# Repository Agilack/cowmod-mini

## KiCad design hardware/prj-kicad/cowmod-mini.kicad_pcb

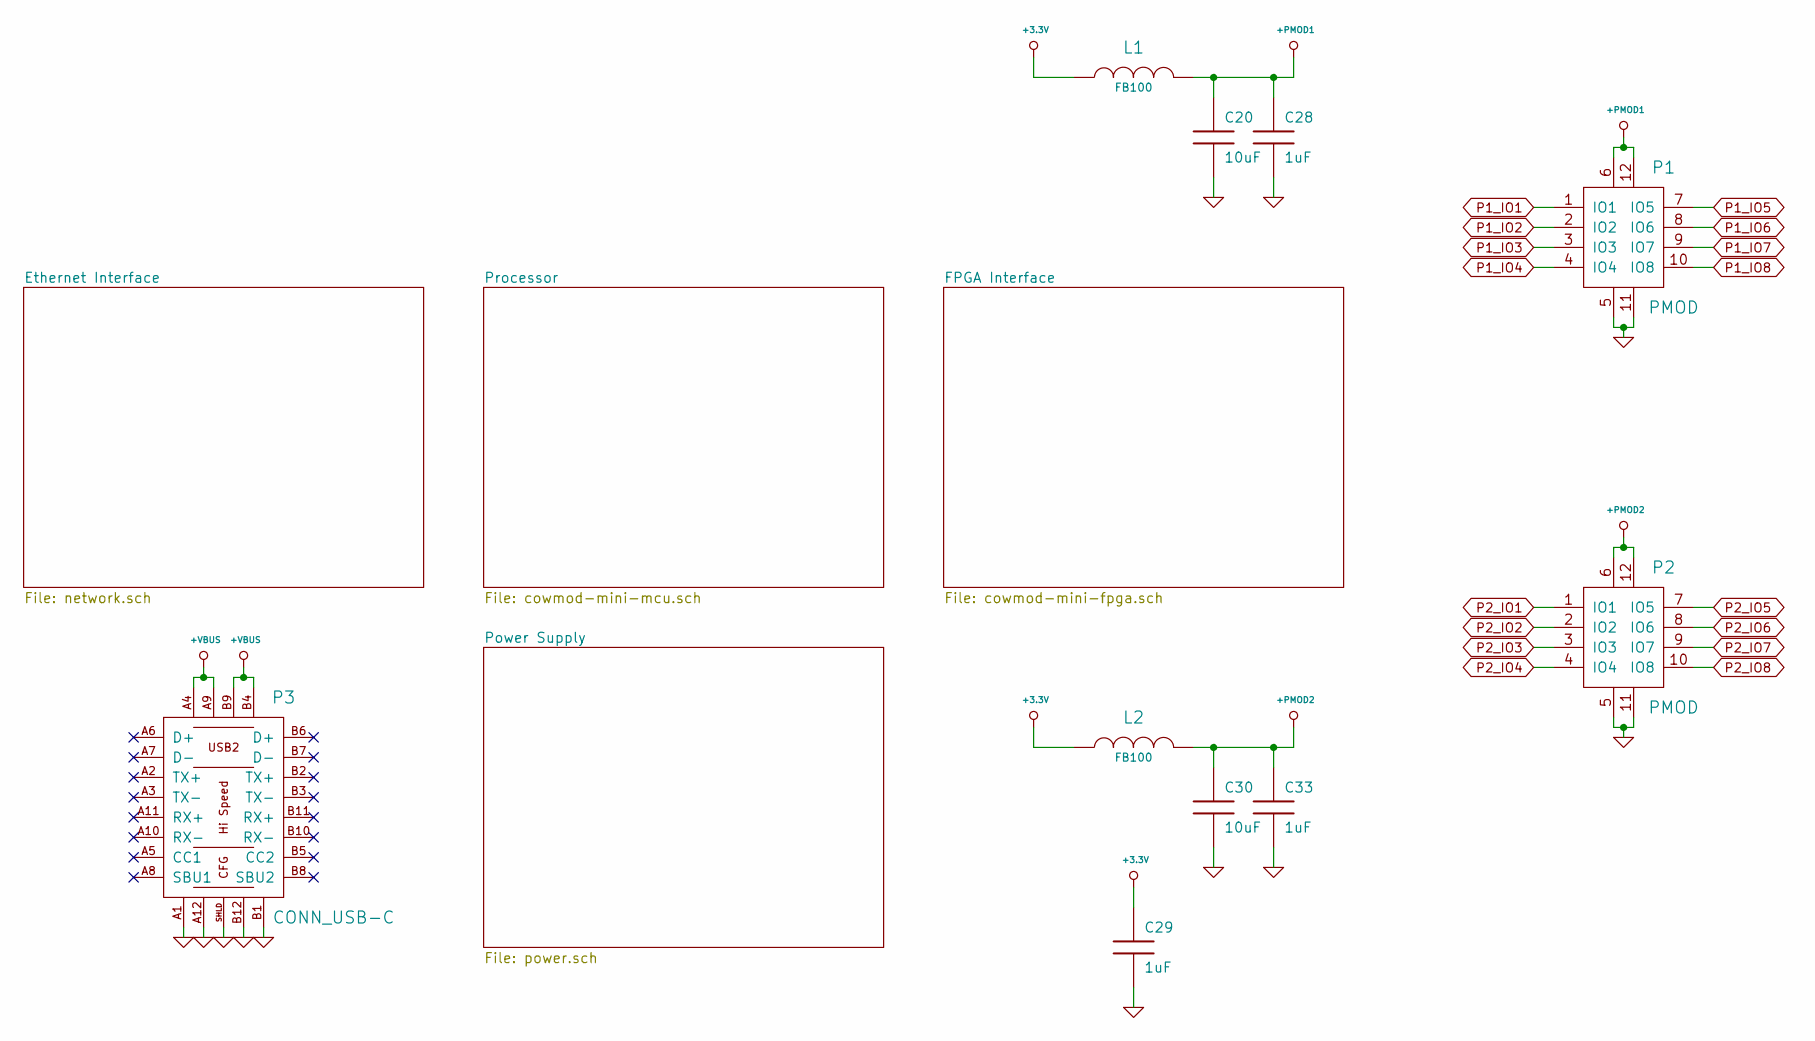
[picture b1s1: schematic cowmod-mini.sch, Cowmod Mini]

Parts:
C20, C30: 10uF; SMD1206
C28, C29, C33: 1uF; SMD0603
L1, L2: FB100; SMD0805
P1, P2: PMOD; PMOD_SSW106-RA
P3: CONN_USB-C; CONN_632723300011

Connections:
+3.3V: C29.1, L1.1, L2.1; also elsewhere on the board
+PMOD1: C20.1, C28.1, L1.2, P1.6, P1.12; also elsewhere on the board
+PMOD2: C30.1, C33.1, L2.2, P2.6, P2.12; also elsewhere on the board
+VBUS: P3.A4, P3.A9, P3.B4, P3.B9; also elsewhere on the board
GND: C20.2, C28.2, C29.2, C30.2, C33.2, P1.5, P1.11, P2.5, P2.11, P3.A1, P3.A12, P3.B1, P3.B12, P3.SHLD; also elsewhere on the board
P1_IO1: P1.1 (IO1); also elsewhere on the board
P1_IO2: P1.2 (IO2); also elsewhere on the board
P1_IO3: P1.3 (IO3); also elsewhere on the board
P1_IO4: P1.4 (IO4); also elsewhere on the board
P1_IO5: P1.7 (IO5); also elsewhere on the board
P1_IO6: P1.8 (IO6); also elsewhere on the board
P1_IO7: P1.9 (IO7); also elsewhere on the board
P1_IO8: P1.10 (IO8); also elsewhere on the board
P2_IO1: P2.1 (IO1); also elsewhere on the board
P2_IO2: P2.2 (IO2); also elsewhere on the board
P2_IO3: P2.3 (IO3); also elsewhere on the board
P2_IO4: P2.4 (IO4); also elsewhere on the board
P2_IO5: P2.7 (IO5); also elsewhere on the board
P2_IO6: P2.8 (IO6); also elsewhere on the board
P2_IO7: P2.9 (IO7); also elsewhere on the board
P2_IO8: P2.10 (IO8); also elsewhere on the board

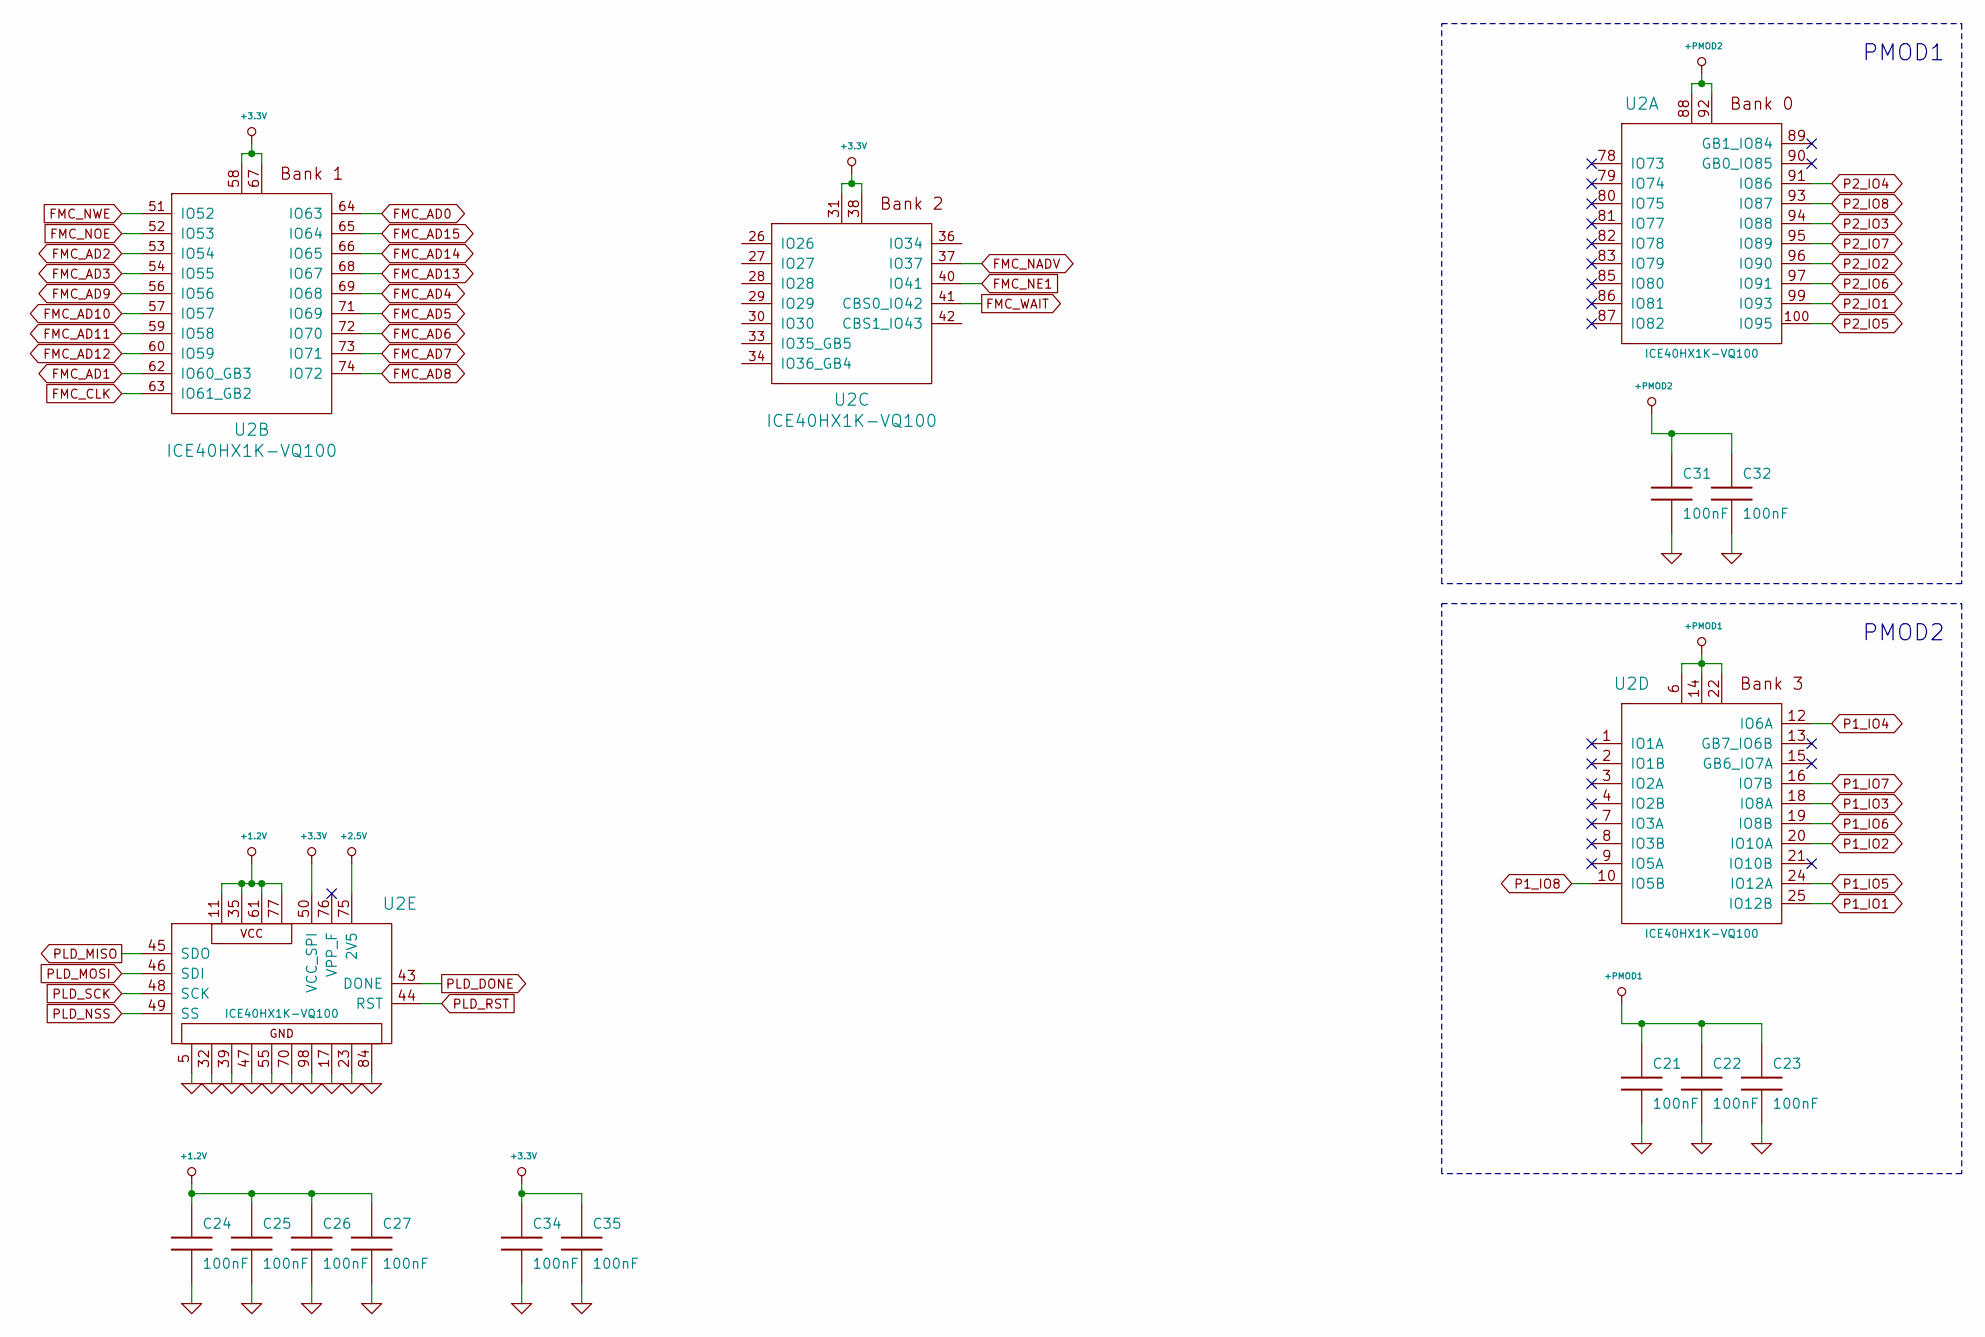
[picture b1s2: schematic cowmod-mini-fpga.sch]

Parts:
C21, C22, C23, C24, C25, C26, C27, C31, C32, C34, C35: 100nF; SMD0603
U2: ICE40HX1K-VQ100; TQFP100

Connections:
+1.2V: C24.1, C25.1, C26.1, C27.1, U2.11, U2.35, U2.61, U2.77; also elsewhere on the board
+2.5V: U2.75 (2V5); also elsewhere on the board
+3.3V: C34.1, C35.1, U2.31, U2.38, U2.50 (VCC_SPI), U2.58, U2.67; also elsewhere on the board
+PMOD1: C21.1, C22.1, C23.1, U2.6, U2.14, U2.22; also elsewhere on the board
+PMOD2: C31.1, C32.1, U2.88, U2.92; also elsewhere on the board
FMC_AD0: U2.64 (IO63); also elsewhere on the board
FMC_AD1: U2.62 (IO60_GB3); also elsewhere on the board
FMC_AD2: U2.53 (IO54); also elsewhere on the board
FMC_AD3: U2.54 (IO55); also elsewhere on the board
FMC_AD4: U2.69 (IO68); also elsewhere on the board
FMC_AD5: U2.71 (IO69); also elsewhere on the board
FMC_AD6: U2.72 (IO70); also elsewhere on the board
FMC_AD7: U2.73 (IO71); also elsewhere on the board
FMC_AD8: U2.74 (IO72); also elsewhere on the board
FMC_AD9: U2.56 (IO56); also elsewhere on the board
FMC_AD10: U2.57 (IO57); also elsewhere on the board
FMC_AD11: U2.59 (IO58); also elsewhere on the board
FMC_AD12: U2.60 (IO59); also elsewhere on the board
FMC_AD13: U2.68 (IO67); also elsewhere on the board
FMC_AD14: U2.66 (IO65); also elsewhere on the board
FMC_AD15: U2.65 (IO64); also elsewhere on the board
FMC_CLK: U2.63 (IO61_GB2); also elsewhere on the board
FMC_NADV: U2.37 (IO37); also elsewhere on the board
FMC_NE1: U2.40 (IO41); also elsewhere on the board
FMC_NOE: U2.52 (IO53); also elsewhere on the board
FMC_NWE: U2.51 (IO52); also elsewhere on the board
FMC_WAIT: U2.41 (CBS0_IO42); also elsewhere on the board
GND: C21.2, C22.2, C23.2, C24.2, C25.2, C26.2, C27.2, C31.2, C32.2, C34.2, C35.2, U2.5, U2.17, U2.23, U2.32, U2.39, U2.47, U2.55, U2.70, U2.84, U2.98; also elsewhere on the board
P1_IO1: U2.25 (IO12B); also elsewhere on the board
P1_IO2: U2.20 (IO10A); also elsewhere on the board
P1_IO3: U2.18 (IO8A); also elsewhere on the board
P1_IO4: U2.12 (IO6A); also elsewhere on the board
P1_IO5: U2.24 (IO12A); also elsewhere on the board
P1_IO6: U2.19 (IO8B); also elsewhere on the board
P1_IO7: U2.16 (IO7B); also elsewhere on the board
P1_IO8: U2.10 (IO5B); also elsewhere on the board
P2_IO1: U2.99 (IO93); also elsewhere on the board
P2_IO2: U2.96 (IO90); also elsewhere on the board
P2_IO3: U2.94 (IO88); also elsewhere on the board
P2_IO4: U2.91 (IO86); also elsewhere on the board
P2_IO5: U2.100 (IO95); also elsewhere on the board
P2_IO6: U2.97 (IO91); also elsewhere on the board
P2_IO7: U2.95 (IO89); also elsewhere on the board
P2_IO8: U2.93 (IO87); also elsewhere on the board
PLD_DONE: U2.43 (DONE); also elsewhere on the board
PLD_MISO: U2.45 (SDO); also elsewhere on the board
PLD_MOSI: U2.46 (SDI); also elsewhere on the board
PLD_NSS: U2.49 (SS); also elsewhere on the board
PLD_RST: U2.44 (RST); also elsewhere on the board
PLD_SCK: U2.48 (SCK); also elsewhere on the board

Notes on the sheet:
PMOD1
PMOD2

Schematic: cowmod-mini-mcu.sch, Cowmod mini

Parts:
C1: 1uF; SMD0603
C4, C5, C6, C7, C8: 100nF; SMD0603
C9, C10: 2.2uF; SMD0603
R1, R2: 10k; SMD0603
TP2, TP3, TP4, TP5: CONN_1; TP_SMD
TP10, TP11: CONN_1; TP_PIN
U1: STM32F750V8; TQFP100
U4: M25P16-VME; SOIC-8E

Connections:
+3.3V: C4.1, C5.1, C6.1, C7.1, C8.1, R2.1, U1.6 (VBAT), U1.11, U1.20 (VREF+), U1.21, U1.27, U1.50, U1.75, U1.100, U4.8; also elsewhere on the board
ETH_CRS_DV: U1.31 (PA7); also elsewhere on the board
ETH_MDC: U1.16 (PC1); also elsewhere on the board
ETH_MDIO: U1.24 (PA2); also elsewhere on the board
ETH_REF_CLK: U1.23 (PA1); also elsewhere on the board
ETH_RST: U1.30 (PA6); also elsewhere on the board
ETH_RXD0: U1.32 (PC4); also elsewhere on the board
ETH_RXD1: U1.33 (PC5); also elsewhere on the board
ETH_TXD0: U1.51 (PB12); also elsewhere on the board
ETH_TXD1: U1.52 (PB13); also elsewhere on the board
ETH_TXEN: U1.47 (PB11); also elsewhere on the board
FMC_AD0: U1.61 (PD14); also elsewhere on the board
FMC_AD1: U1.62 (PD15); also elsewhere on the board
FMC_AD2: U1.81 (PD0); also elsewhere on the board
FMC_AD3: U1.82 (PD1); also elsewhere on the board
FMC_AD4: U1.37 (PE7); also elsewhere on the board
FMC_AD5: U1.38 (PE8); also elsewhere on the board
FMC_AD6: U1.39 (PE9); also elsewhere on the board
FMC_AD7: U1.40 (PE10); also elsewhere on the board
FMC_AD8: U1.41 (PE11); also elsewhere on the board
FMC_AD9: U1.42 (PE12); also elsewhere on the board
FMC_AD10: U1.43 (PE13); also elsewhere on the board
FMC_AD11: U1.44 (PE14); also elsewhere on the board
FMC_AD12: U1.45 (PE15); also elsewhere on the board
FMC_AD13: U1.55 (PD8); also elsewhere on the board
FMC_AD14: U1.56 (PD9); also elsewhere on the board
FMC_AD15: U1.57 (PD10); also elsewhere on the board
FMC_CLK: U1.84 (PD3); also elsewhere on the board
FMC_NADV: U1.93 (PB7); also elsewhere on the board
FMC_NE1: U1.88 (PD7); also elsewhere on the board
FMC_NOE: U1.85 (PD4); also elsewhere on the board
FMC_NWE: U1.86 (PD5); also elsewhere on the board
FMC_WAIT: U1.87 (PD6); also elsewhere on the board
GND: C1.2, C4.2, C5.2, C6.2, C7.2, C8.2, C9.2, C10.2, R1.2, TP5.1, TP11.1, U1.10, U1.19, U1.26, U1.49, U1.74, U1.99, U4.4; also elsewhere on the board
MEM_CLK: U1.36 (PB2), U4.6 (CLK)
MEM_CS: U1.92 (PB6), U4.1 (CS)
MEM_IO0: U1.66 (PC9), U4.5 (IO0_DI)
MEM_IO1: U1.59 (PD12), U4.2 (IO1_DO)
MEM_IO2: U1.1 (PE2), U4.3 (IO2_WP)
MEM_IO3: U1.60 (PD13), U4.7 (IO3_HOLD)
unnamed: C9.1, U1.48 (VCAP1)
unnamed: C10.1, U1.73 (VCAP2)
unnamed: R1.1, U1.94 (BOOT0)
unnamed: TP10.1, U1.63 (PC6)
PLD_CAUX: U1.67 (PA8)
PLD_DONE: U1.89 (PB3); also elsewhere on the board
PLD_MISO: U1.79 (PC11); also elsewhere on the board
PLD_MOSI: U1.80 (PC12); also elsewhere on the board
PLD_NSS: U1.77 (PA15); also elsewhere on the board
PLD_RST: U1.83 (PD2); also elsewhere on the board
PLD_SCK: U1.78 (PC10); also elsewhere on the board
RST: C1.1, R2.2, TP4.1, U1.14 (RST)
SWD_CLK: TP2.1, U1.76 (PA14)
SWD_IO: TP3.1, U1.72 (PA13)

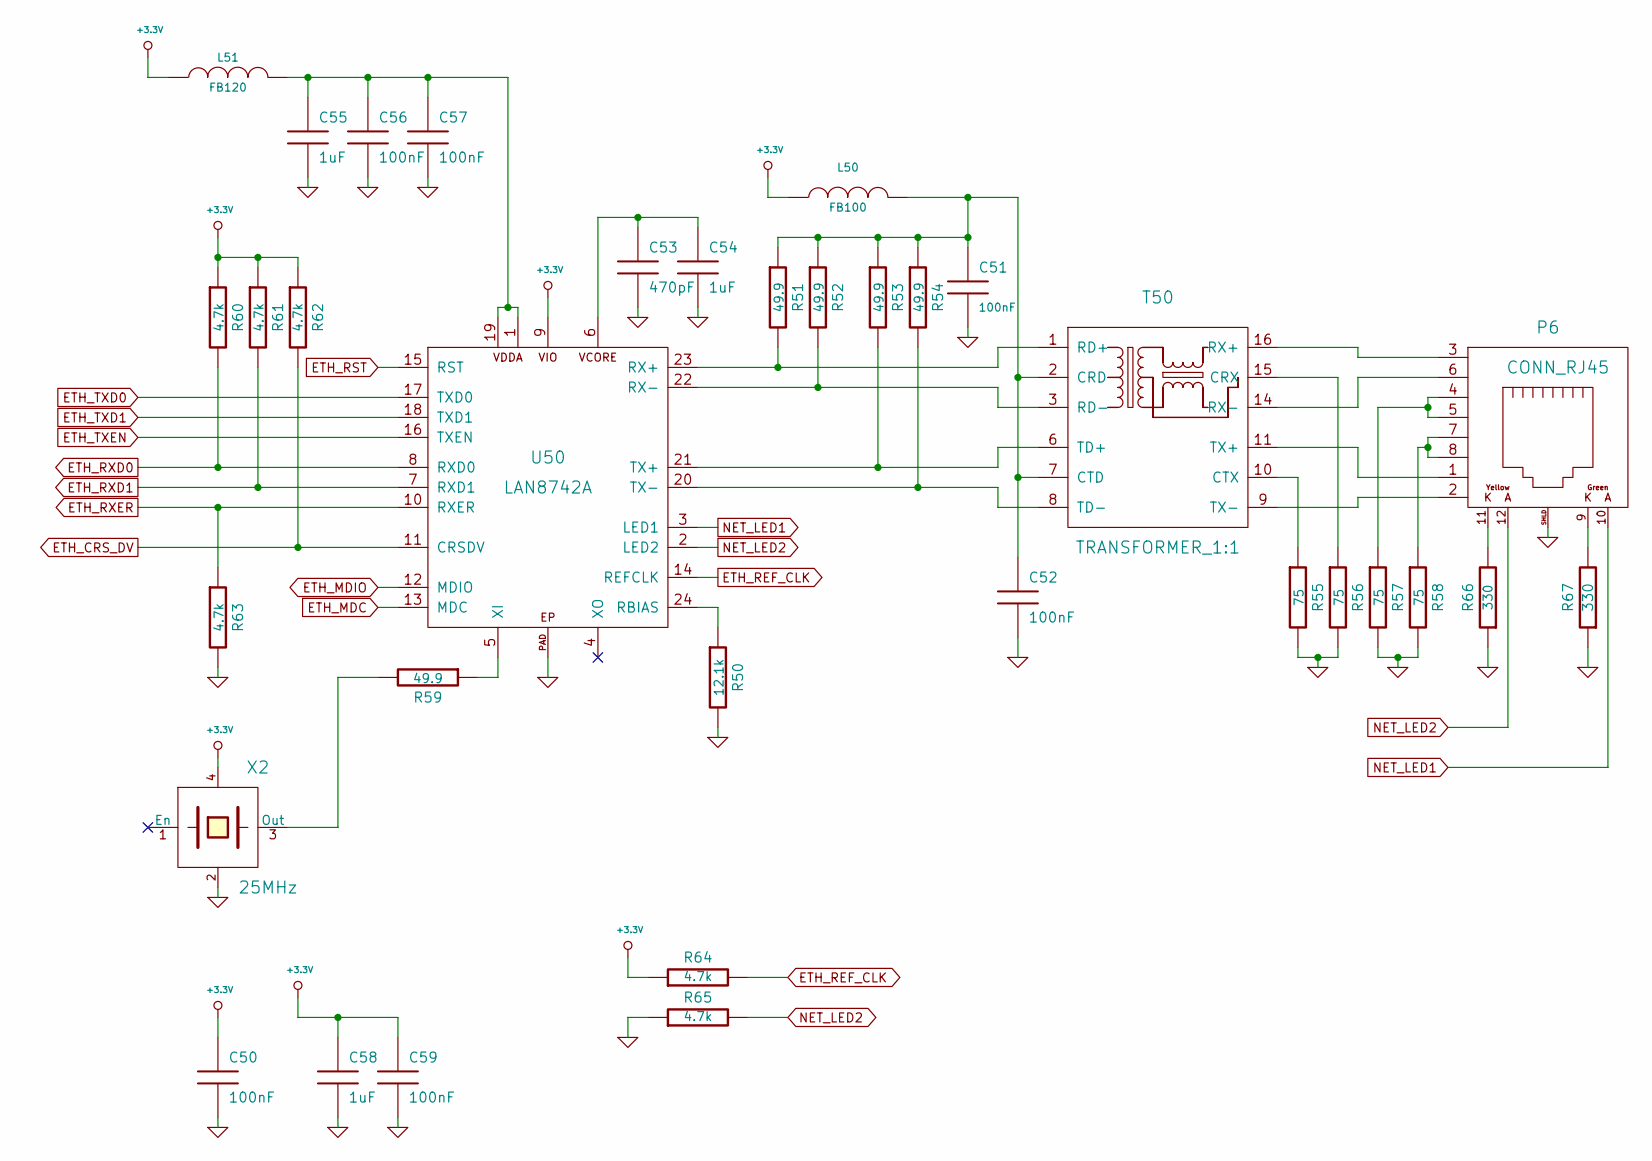
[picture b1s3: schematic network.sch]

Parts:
C50, C51, C52, C56, C57, C59: 100nF; SMD0603
C53: 470pF; SMD0603
C54, C55, C58: 1uF; SMD0603
L50: FB100; SMD0603
L51: FB120; SMD0603
P6: CONN_RJ45; CONN_615008185121
R50: 12.1k; SMD0603
R51, R52, R53, R54, R59: 49.9; SMD0603
R55, R56, R57, R58: 75; SMD0603
R60, R61, R62, R63, R64, R65: 4.7k; SMD0603
R66, R67: 330; SMD0603
T50: TRANSFORMER_1:1; TR_W749013011
U50: LAN8742A; QFN24
X2: 25MHz; Q_SMD5x3

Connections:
+3.3V: C50.1, C58.1, C59.1, L50.1, L51.1, R60.1, R61.1, R62.1, R64.1, U50.9, X2.4; also elsewhere on the board
ETH_CRS_DV: R62.2, U50.11 (CRSDV); also elsewhere on the board
ETH_MDC: U50.13 (MDC); also elsewhere on the board
ETH_MDIO: U50.12 (MDIO); also elsewhere on the board
ETH_REF_CLK: R64.2, U50.14 (REFCLK); also elsewhere on the board
ETH_RST: U50.15 (RST); also elsewhere on the board
ETH_RXD0: R60.2, U50.8 (RXD0); also elsewhere on the board
ETH_RXD1: R61.2, U50.7 (RXD1); also elsewhere on the board
ETH_RXER: R63.1, U50.10 (RXER)
ETH_TXD0: U50.17 (TXD0); also elsewhere on the board
ETH_TXD1: U50.18 (TXD1); also elsewhere on the board
ETH_TXEN: U50.16 (TXEN); also elsewhere on the board
GND: C50.2, C51.2, C52.2, C53.2, C54.2, C55.2, C56.2, C57.2, C58.2, C59.2, P6.SHLD, R50.2, R55.2, R56.2, R57.2, R58.2, R63.2, R65.1, R66.1, R67.1, U50.PAD, X2.2; also elsewhere on the board
NET_LED1: P6.10, U50.3 (LED1)
NET_LED2: P6.12, R65.2, U50.2 (LED2)
unnamed: C51.1, C52.1, L50.2, R51.1, R52.1, R53.1, R54.1, T50.2 (CRD), T50.7 (CTD)
unnamed: C53.1, C54.1, U50.6
unnamed: C55.1, C56.1, C57.1, L51.2, U50.1, U50.19
unnamed: P6.1, T50.11 (TX+)
unnamed: P6.2, T50.9 (TX-)
unnamed: P6.3, T50.16 (RX+)
unnamed: P6.4, P6.5, R57.1
unnamed: P6.6, T50.14 (RX-)
unnamed: P6.7, P6.8, R58.1
unnamed: P6.9, R67.2
unnamed: P6.11, R66.2
unnamed: R50.1, U50.24 (RBIAS)
unnamed: R51.2, T50.1 (RD+), U50.23 (RX+)
unnamed: R52.2, T50.3 (RD-), U50.22 (RX-)
unnamed: R53.2, T50.6 (TD+), U50.21 (TX+)
unnamed: R54.2, T50.8 (TD-), U50.20 (TX-)
unnamed: R55.1, T50.10 (CTX)
unnamed: R56.1, T50.15 (CRX)
unnamed: R59.1, U50.5 (XI)
unnamed: R59.2, X2.3 (Out)

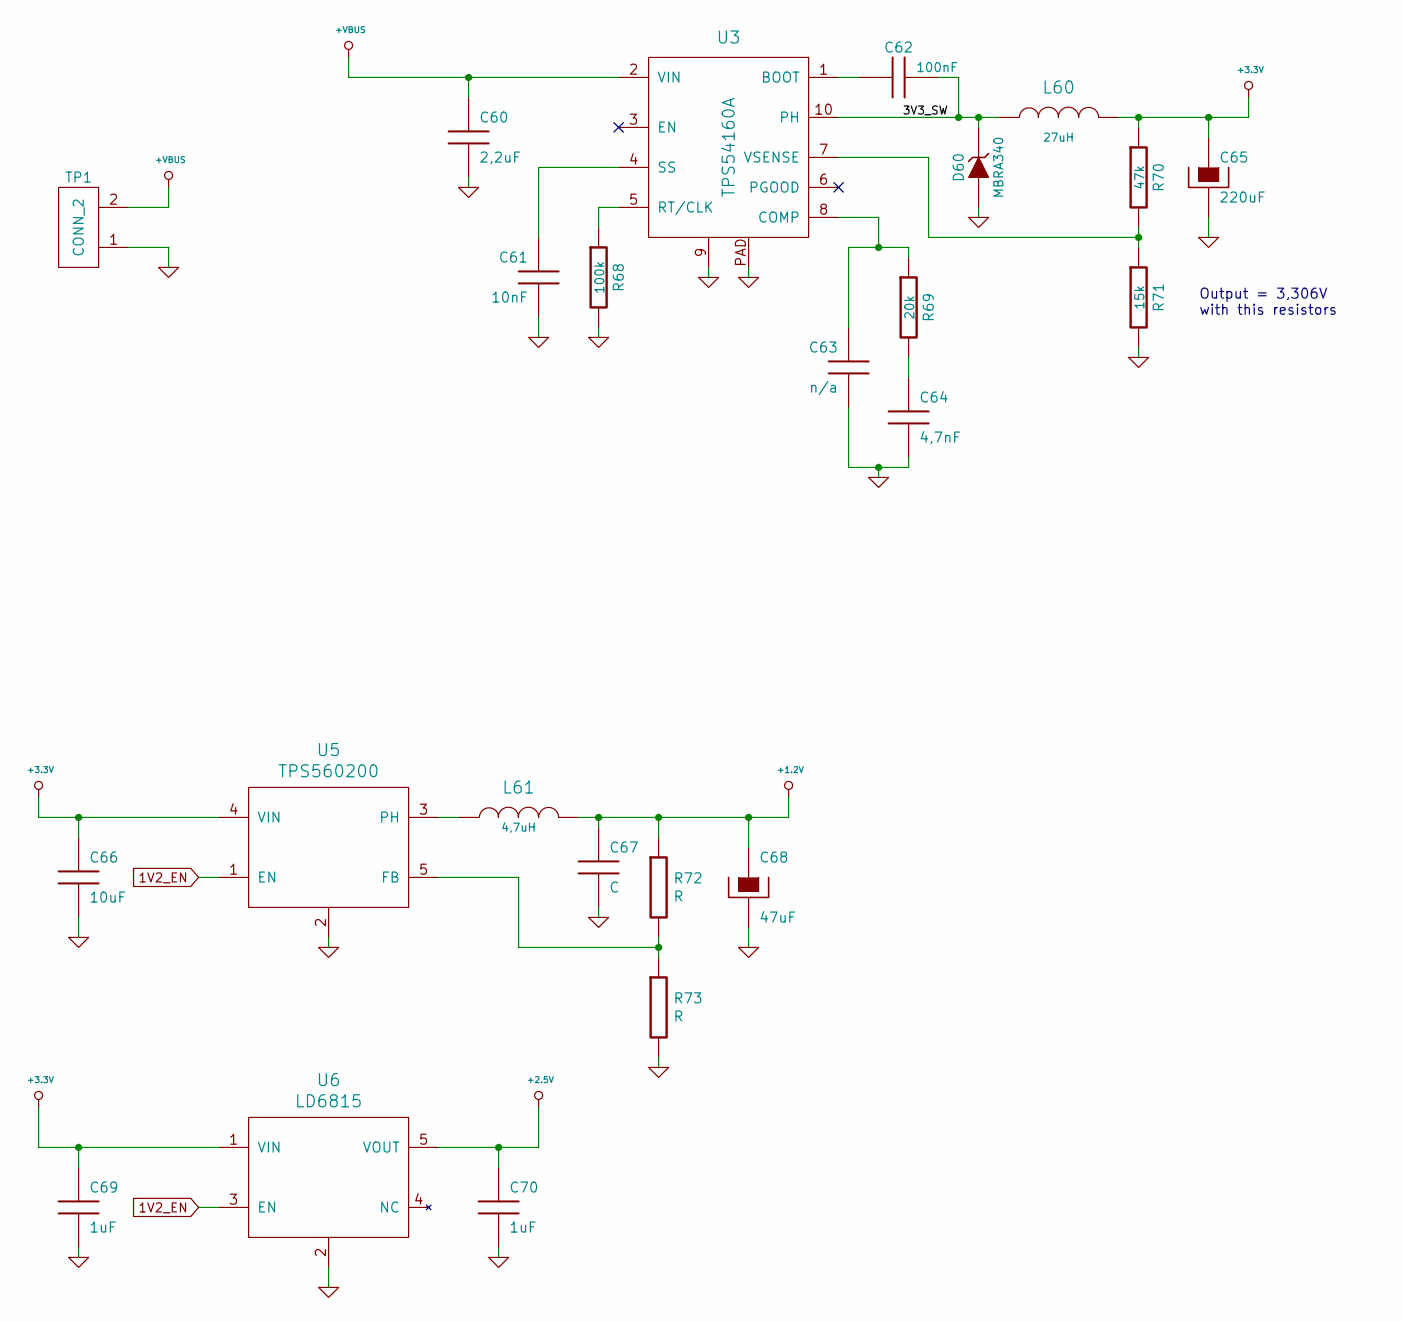
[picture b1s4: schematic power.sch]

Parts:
C60: 2,2uF; C_1210
C61: 10nF; SMD0603
C62: 100nF; SMD0603
C63: n/a; SMD0603
C64: 4,7nF; SMD0603
C65: 220uF; C_TPB_D4
C66: 10uF; SMD1206
C67: C; SMD0603
C68: 47uF; C_1210
C69, C70: 1uF; SMD0603
D60: MBRA340; DO214AC
L60: 27uH; I_MSS1048
L61: 4,7uH; I_TYS4012
R68: 100k; SMD0603
R69: 20k; SMD0603
R70: 47k; SMD0603
R71: 15k; SMD0603
R72, R73: R; SMD0603
TP1: CONN_2
U3: TPS54160A; MSOP10p
U5: TPS560200; SOT23-5
U6: LD6815; SOT23-5

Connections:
1V2_EN: U5.1 (EN), U6.3 (EN)
+1.2V: C67.1, C68.1, L61.2, R72.1; also elsewhere on the board
+2.5V: C70.1, U6.5 (VOUT); also elsewhere on the board
+3.3V: C65.1, C66.1, C69.1, L60.2, R70.1, U5.4 (VIN), U6.1 (VIN); also elsewhere on the board
+VBUS: C60.1, TP1.2, U3.2 (VIN); also elsewhere on the board
/Power Supply/3V3_SW: C62.2, D60.2 (K), L60.1, U3.10 (PH)
GND: C60.2, C61.2, C63.2, C64.2, C65.2, C66.2, C67.2, C68.2, C69.2, C70.2, D60.1 (A), R68.2, R71.2, R73.2, TP1.1, U3.9, U3.PAD, U5.2, U6.2; also elsewhere on the board
unnamed: C61.1, U3.4 (SS)
unnamed: C62.1, U3.1 (BOOT)
unnamed: C63.1, R69.1, U3.8 (COMP)
unnamed: C64.1, R69.2
unnamed: L61.1, U5.3 (PH)
unnamed: R68.1, U3.5 (RT/CLK)
unnamed: R70.2, R71.1, U3.7 (VSENSE)
unnamed: R72.2, R73.1, U5.5 (FB)

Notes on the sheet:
Output = 3,306V with this resistors

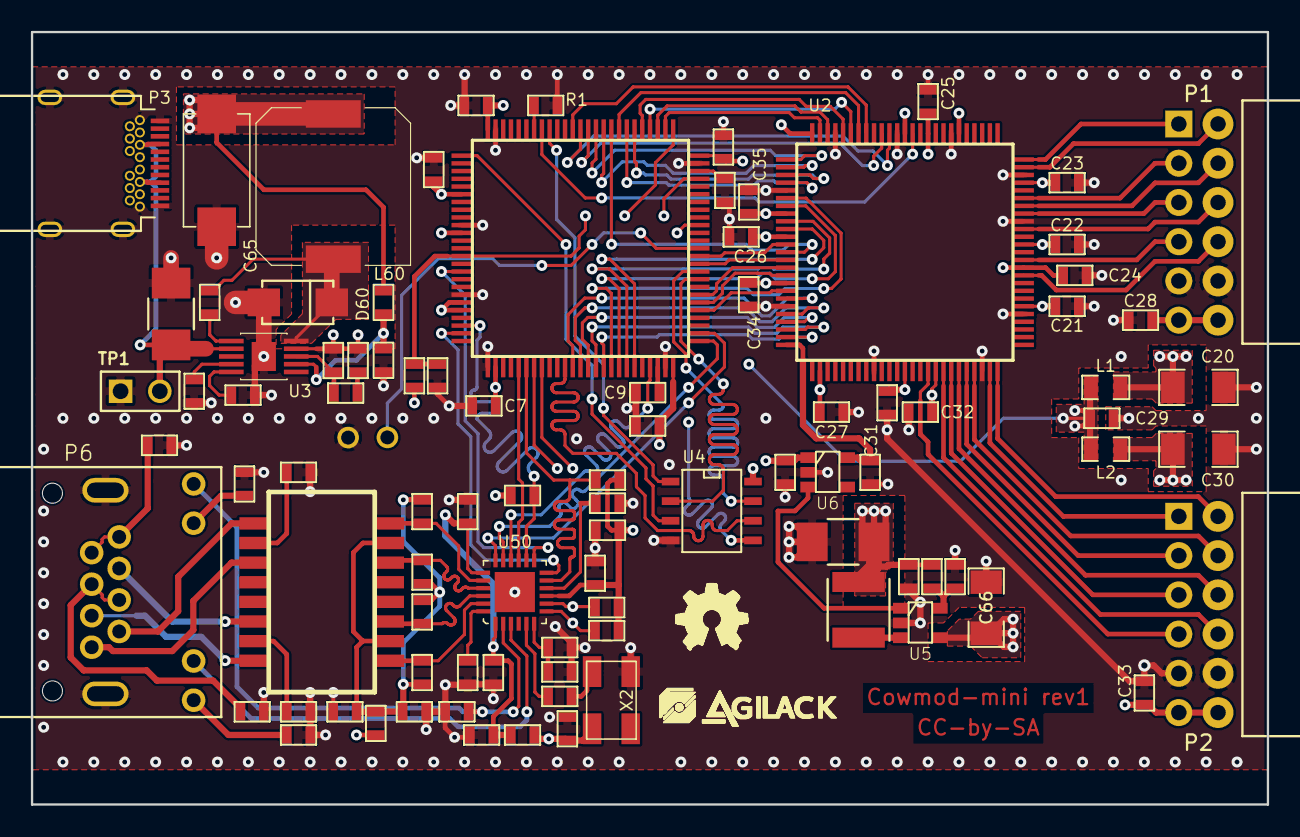
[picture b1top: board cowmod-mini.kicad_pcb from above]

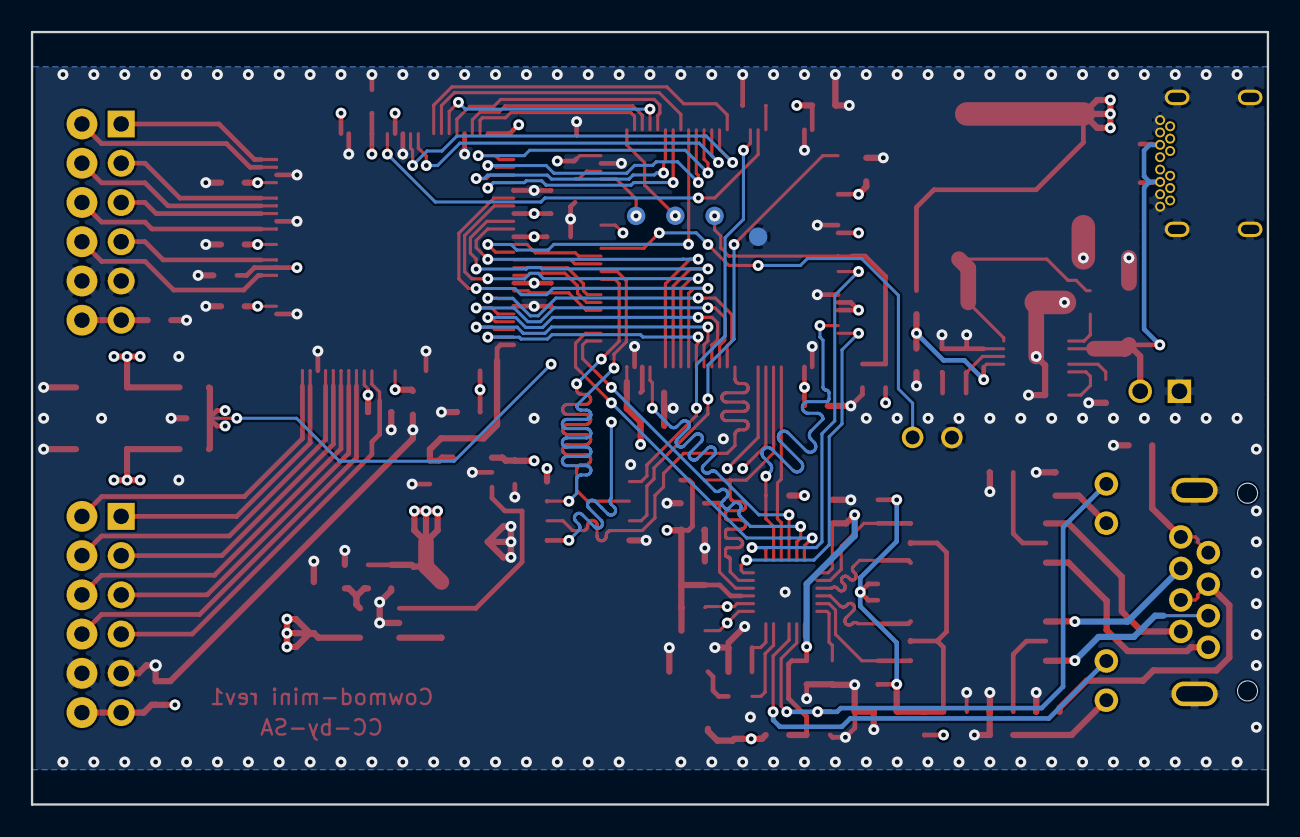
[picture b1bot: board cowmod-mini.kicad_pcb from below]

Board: 4 copper layers, 80.0 x 50.0 mm, 100 parts (4 on the bottom side), 107 nets.

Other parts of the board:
agilack-11.5: 450px; logo-agilack-11.5
ohw_logo: VAL**; logo-ohw

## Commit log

2020-02-03 --=={ Create project }==--
2020-02-04 = ADD: Insert FPGA to drive external PMOD interfaces
2020-02-05 = ADD: Insert MCU and connect it to FPGA
2020-02-06 = ADD: Insert ethernet network interface
2020-02-07 = ADD: Insert power supply regulators (3V3 / 1V2 / 2V5)
2020-02-09 = ADD: Insert an SPI flash for MCU
2020-02-15 = UPD: Add missing reset circuit, debug port and simple UART console

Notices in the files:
hardware/prj-kicad/cowmod-mini.kicad_pcb:
CC-by-SA
